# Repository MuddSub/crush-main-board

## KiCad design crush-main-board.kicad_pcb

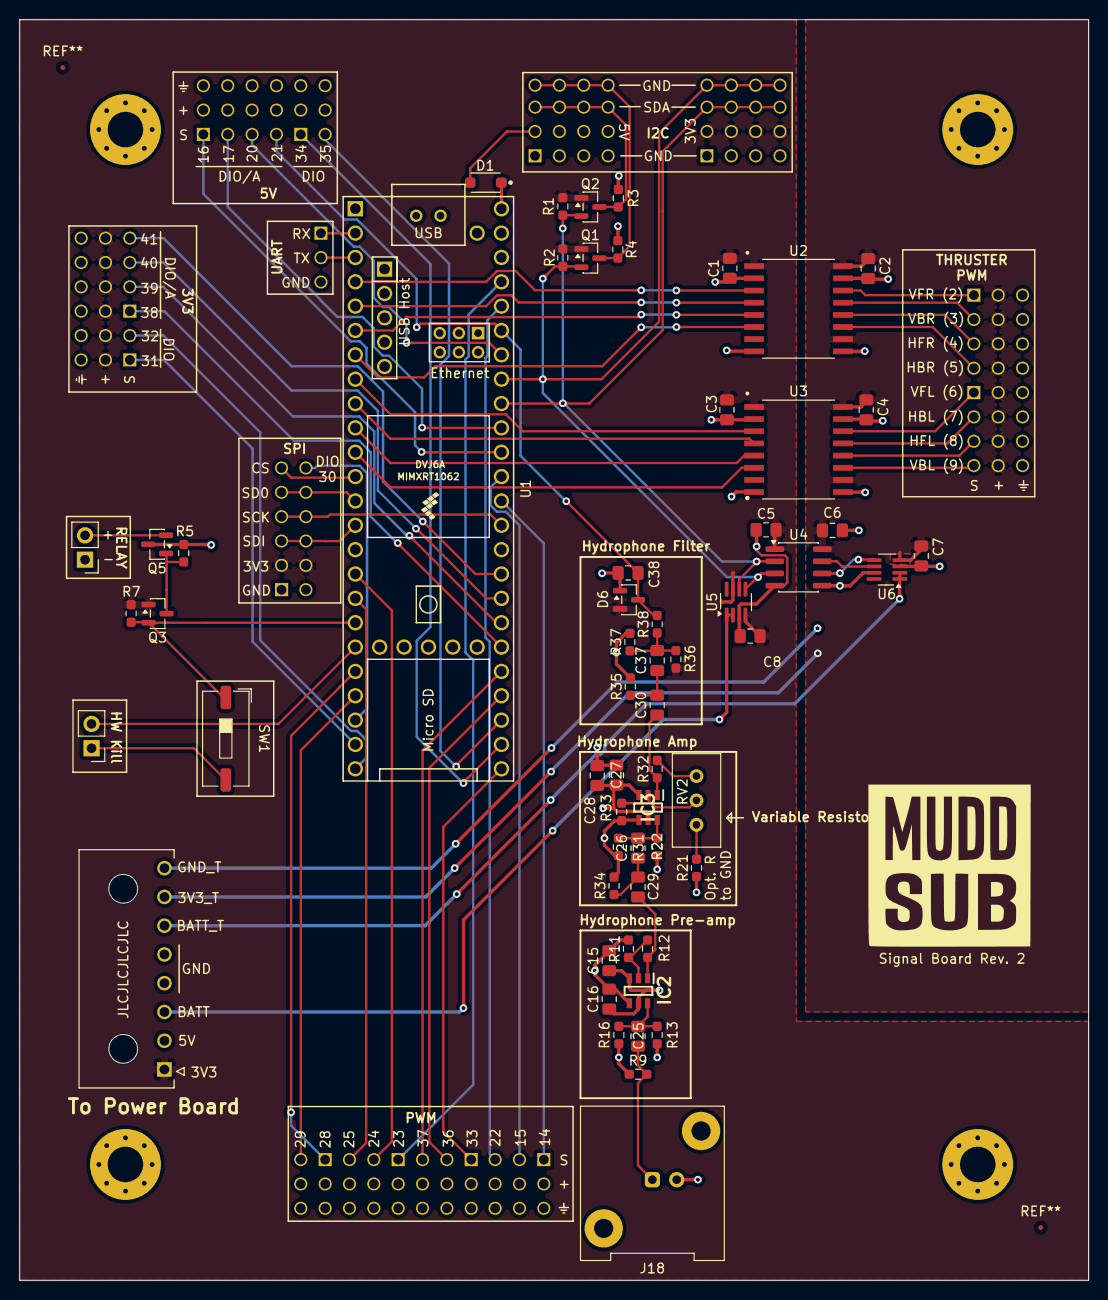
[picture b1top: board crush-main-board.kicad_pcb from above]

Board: 4 copper layers, 111.5 x 131.5 mm, 77 parts (0 on the bottom side), 77 nets.

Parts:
C1, C2, C3, C4, C5, C6, C7, C8: 0u1; C_0805_2012Metric_Pad1.18x1.45mm_HandSolder
C15, C27: 100n; C_0805_2012Metric_Pad1.18x1.45mm_HandSolder
C16, C28, C29, C30: 10n; C_0805_2012Metric_Pad1.18x1.45mm_HandSolder
C25, C26, C37: 1m; C_0805_2012Metric_Pad1.18x1.45mm_HandSolder
C38: 2.2n; C_0805_2012Metric_Pad1.18x1.45mm_HandSolder
D1: SM5817PL-TP; SODFL3718X108N
D6: BAT54S; SOT-23
H1, H2, H3, H4: MountingHole_Pad; MountingHole_3.7mm_Pad_Via
IC2, IC3: LT6200CS6#TRMPBF; SOT95P280X100-6N
J1, J2: 4x4_Header
J3: 6x2_Header
J4: 3x1_Header
J5, J6, J12: 3x2 Header; 3x2_Header
J7, J8: 3x4 Header; 3x4_Header
J9, J10, J11: 3x3 Header; 3x3_Header
J13, J14: 3x4_Header
J15: 2157601008; MOLEX_2157601008
J16, J17: Conn_01x02; PinHeader_1x02_P2.54mm_Vertical
J18: Conn_Coaxial; BNC_Amphenol_031-5539_Vertical
Q1, Q2, Q3: BSN20; SOT-23
Q5: DMG2301L; SOT-23
R1, R2, R3, R4, R5, R7: 2k4; R_0603_1608Metric_Pad0.98x0.95mm_HandSolder
R9: r=50; R_0603_1608Metric_Pad0.98x0.95mm_HandSolder
R11, R16, R31, R33: 1k; R_0603_1608Metric_Pad0.98x0.95mm_HandSolder
R12, R13, R32, R34, R35: 100k; R_0603_1608Metric_Pad0.98x0.95mm_HandSolder
R21: r=100k; R_0603_1608Metric_Pad0.98x0.95mm_HandSolder
R22: 1Meg; R_0603_1608Metric_Pad0.98x0.95mm_HandSolder
R36, R37: 10k; R_0603_1608Metric_Pad0.98x0.95mm_HandSolder
R38: r=1k; R_0603_1608Metric_Pad0.98x0.95mm_HandSolder
RV2: R_Potentiometer_Trim; Potentiometer_Bourns_3296W_Vertical
SW1: SW_SPST; SW_DIP_SPSTx01_Slide_9.78x4.72mm_W8.61mm_P2.54mm
U1: Teensy4.1; Teensy41
U2, U3: ISO7740DW; SOIC127P1030X265-16N
U4: ISO1640BDR; SOIC-8_3.9x4.9mm_P1.27mm
U5, U6: INA232B; SOT-23-8_Handsoldering

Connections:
+3V3: C1.2, C3.2, C5.2, C8.2, D6.2 (K), J1.02, J1.06, J1.10, J1.14, J3.02, J3.08, J5.02, J5.05, J7.02, J7.05, J7.08, J7.11, J15.1, Q1.1 (G), Q2.1 (G), Q3.1 (G), R1.1, R2.1, R7.1, R36.1, U2.1 (VCC1), U3.1 (VCC1), U4.1 (VCC1), U5.4 (VS), U5.7 (A0)
+3V3_T: C2.2, C4.2, C6.2, C7.2, J13.02, J13.05, J13.08, J13.11, J14.02, J14.05, J14.08, J14.11, J15.7, U2.10 (EN2), U2.16 (VCC2), U3.10 (EN2), U3.16 (VCC2), U4.8 (VCC2), U6.4 (VS)
+5V: C15.1, C16.1, C27.1, C28.1, D1.2 (A), IC2.3 (+IN), IC2.5 (~SHDN), IC3.3 (+IN), IC3.5 (~SHDN), J2.02, J2.06, J2.10, J2.14, J6.02, J6.05, J8.02, J8.05, J8.08, J8.11, J9.02, J9.05, J9.08, J10.02, J10.05, J10.08, J11.02, J11.05, J11.08, J12.02, J12.05, J15.2, Q5.3 (D), R3.1, R4.1, R5.1, R13.1, R22.1
/+RELAY: J17.2, Q5.2 (S)
/SCL_T: U4.6 (SCL2), U6.5 (SCL)
/SDA_T: U4.7 (SDA2), U6.6 (SDA)
A/DIO16: J8.01, U1.38 (16_A2_RX4_SCL1)
A/DIO17: J8.04, U1.39 (17_A3_TX4_SDA1)
A/DIO20: J8.07, U1.42 (20_A6_TX5_LRCLK1)
A/DIO21: C38.1, D6.3 (COM), J8.10, R38.2, U1.43 (21_A7_RX5_BCLK1)
A/DIO26: Q3.2 (S), R7.2, SW1.1 (A), U1.18 (26_A12_MOSI1)
A/DIO38: J7.01, U1.30 (38_CS1_IN1)
A/DIO39: J7.04, U1.31 (39_MISO1_OUT1A)
A/DIO40: J7.07, U1.32 (40_A16)
A/DIO41: J7.10, U1.33 (41_A17)
BATT: J15.3, U5.1 (Vin+), U5.2 (Vin-)
BATT_T: J15.6, U6.1 (Vin+), U6.2 (Vin-)
BNC_OUT: C25.1, J18.1 (In), R9.2
DIO30: J3.12, U1.22 (30_CRX3)
DIO31: J5.01, U1.23 (31_CTX3)
DIO32: J5.04, U1.24 (32_OUT1B)
DIO34: J6.01, U1.26 (34_RX8)
DIO35: J6.04, U1.27 (35_TX8)
GND: C1.1, C3.1, C5.1, C8.1, C15.2, C16.2, C27.2, C28.2, C38.2, D6.1 (A), H1.1 (1_1), H2.1 (1_1), H3.1 (1_1), H4.1 (1_1), IC2.4 (-IN), IC3.4 (-IN), J1.01, J1.05, J1.09, J1.13, J2.01, J2.05, J2.09, J2.13, J3.01, J3.07, J4.03, J5.03, J5.06, J6.03, J6.06, J7.03, J7.06, J7.09, J7.12, J8.03, J8.06, J8.09, J8.12, J9.03, J9.06, J9.09, J10.03, J10.06, J10.09, J11.03, J11.06, J11.09, J12.03, J12.06, J15.5, J17.1, J18.2 (Ext), R9.1, R11.2, R16.2, R21.1, R31.2, R33.2, R34.2, R35.2, R37.2, U1.1 (GND), U1.34 (GND), U1.47 (GND), U1.58 (GND), U1.59 (GND), U2.2 (GND1), U2.8 (GND1), U3.2 (GND1), U3.8 (GND1), U4.4 (GND1), U5.3 (GND)
GND_T: C2.1, C4.1, C6.1, C7.1, J13.03, J13.06, J13.09, J13.12, J14.03, J14.06, J14.09, J14.12, J15.8, U2.9 (GND2), U2.15 (GND2), U3.9 (GND2), U3.15 (GND2), U4.5 (GND2), U6.3 (GND), U6.7 (A0)
HW_KILL_1: J16.2, U1.19 (27_A13_SCK1)
HW_KILL_2: J16.1, SW1.2 (B)
unnamed: C26.1, C29.2, R34.1
unnamed: C30.2, C37.1, R35.1
unnamed: C37.2, R36.2, R37.1, R38.1
unnamed: D1.1 (K), U1.48 (VIN)
unnamed: C25.2, IC2.6 (V+), R13.2, R16.1
unnamed: IC2.2 (V-), R11.1, R12.2
unnamed: C26.2, IC3.6 (V+), R22.2, R31.1
unnamed: IC3.2 (V-), R33.1, RV2.2
unnamed: Q3.3 (D), Q5.1 (G), R5.2
unnamed: R21.2, RV2.3
unnamed: R32.2, RV2.1
PWM2: U1.4 (2_OUT2), U2.3 (INA)
PWM2_T: J13.01, U2.14 (OUTA)
PWM3: U1.5 (3_LRCLK2), U2.4 (INB)
PWM3_T: J13.04, U2.13 (OUTB)
PWM4: U1.6 (4_BCLK2), U2.5 (INC)
PWM4_T: J13.07, U2.12 (OUTC)
PWM5: U1.7 (5_IN2), U2.6 (IND)
PWM5_T: J13.10, U2.11 (OUTD)
PWM6: U1.8 (6_OUT1D), U3.3 (INA)
PWM6_T: J14.01, U3.14 (OUTA)
PWM7: U1.9 (7_RX2_OUT1A), U3.4 (INB)
PWM7_T: J14.04, U3.13 (OUTB)
PWM8: U1.10 (8_TX2_IN1), U3.5 (INC)
PWM8_T: J14.07, U3.12 (OUTC)
PWM9: U1.11 (9_OUT1C), U3.6 (IND)
PWM9_T: J14.10, U3.11 (OUTD)
PWM14: J9.01, U1.36 (14_A0_TX3_SPDIF_OUT)
PWM15: J9.04, U1.37 (15_A1_RX3_SPDIF_IN)
PWM22: J9.07, U1.44 (22_A8_CTX1)
PWM23: J10.01, U1.45 (23_A9_CRX1_MCLK1)
PWM24: J10.04, U1.16 (24_A10_TX6_SCL2)
PWM25: J10.07, U1.17 (25_A11_RX6_SDA2)
PWM28: J12.01, U1.20 (28_RX7)
PWM29: J12.04, U1.21 (29_TX7)
PWM33: J11.01, U1.25 (33_MCLK2)
PWM36: J11.04, U1.28 (36_CS)
PWM37: J11.07, U1.29 (37_CS)
SCL_3V3: J1.04, J1.08, J1.12, J1.16, Q1.2 (S), R2.2, U1.41 (19_A5_SCL), U4.3 (SCL1), U5.5 (SCL)
SCL_5V: J2.04, J2.08, J2.12, J2.16, Q1.3 (D), R4.2
SDA_3V3: J1.03, J1.07, J1.11, J1.15, Q2.2 (S), R1.2, U1.40 (18_A4_SDA), U4.2 (SDA1), U5.6 (SDA)
SDA_5V: J2.03, J2.07, J2.11, J2.15, Q2.3 (D), R3.2
SPI_CS: J3.06, U1.12 (10_CS_MQSR)
SPI_SCK: J3.04, J3.10, U1.35 (13_SCK_LED)
SPI_SDI: J3.03, J3.09, U1.14 (12_MISO_MQSL)
SPI_SDO: J3.05, J3.11, U1.13 (11_MOSI_CTX1)
UART_RX: J4.01, U1.2 (0_RX1_CRX2_CS1)
UART_TX: J4.02, U1.3 (1_TX1_CTX2_MISO1)
VOUT_AMP: C30.1, IC3.1 (OUT), R32.1
VOUT_PREAMP: C29.1, IC2.1 (OUT), R12.1

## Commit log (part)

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2023-02-26 First Commit, WIP
2023-02-27 2/26 Work as a team
2023-02-27 baby change to test committing
2023-02-27 deleted unnecessary files
2023-03-12 Added Digital Isolators
2023-03-26 Add labels for teensy ports
2023-03-26 Update custom library and add PWM headers
2023-03-27 Library Update
    Add the footprint library named "Crush_Mainboard_Footprints.pretty" in the library folder
2023-03-27 Header Arrangement
    Add headers for the remaining pins and attach the custom footprints
2023-03-31 Cleaned up the repo and added Teensy 4.1 to the Crush project library
2023-04-01 Deleted some unnecessary files that were renamed
2023-04-02 Update library with default footprints
2023-04-03 Add SPI, UART, ESC Headers; Fixed library stuff
2023-04-03 Fixed .gitignore and removed backup folders from repo
2023-04-03 Cleaned up the schematic layout & separated the footprints into corresponding groups
2023-04-03 Clean up some minor details in the symbol and footprint library
2023-04-09 Fixed SPI header and updated footprint accordingly
2023-04-10 Removed USB connector (deemed unnecessary) as well as added infrastructure for a battery monitoring circuit
2023-04-10 Added thruster battery monitoring circuit
    There is no footprint assigned for an I2C isolator and resistors yet
2023-04-10 fixed some minor error
2023-04-10 added electrical side battery monitor in case we don't use Teensy's ADC
2023-04-17 Added diode and header for remaining pins, fixed signal battery monitor
2023-04-17 Changed resistor and capacitor footprints to 0603
2023-04-23 Added library for MOLEX inter-board connector
2023-04-23 Added connection to the power board; and the remaining footprints
2023-04-24 Fixed an error of the "3V3_T" and "GND_T" and added some conditions for the PCB design
    The power nets for the thruster side require their own custom symbols unless they will refer to the same ones that are linked to the normal power nets
2023-04-25 Fixed some minor errors and arranged the components into two ground sides
2023-04-26 arranged all components to be ready for routing
2023-04-27 re-aligned the elements based on their grounds
2023-09-30 update i2c level shifter
    * Change resistors from 4.7k to 2.4k to improve signal quality
    * Connect SCL MOSFET gate to 3.3V rather than 5V
2023-11-04 Add battery monitoring circuit using INA233
2023-11-04 minor visual change
2023-11-04 Add shunt capacitor for INA233
2023-11-04 Sketch out a possible circuit for the killswitch
2023-11-11 Switch to INA232
2023-11-18 Fix killswitch circuit
2023-11-18 Fix overlapping wires
2023-11-18 Add levelshifter textbox label
2023-12-02 Changed driving of relay to account for relay loading
2024-02-17 Updated reference for current monitoring chip
2024-02-17 Added JLCPCB Design Rule Check
2024-02-18 Wire up the relay killswitch with JSTs
    In the schematic
2024-02-25 Start laying out main board
2024-03-23 Add monitor for signal battery
2024-03-23 Add changes to pcb
2024-04-06 fixed janky wire in killswitch subcircuit
2024-04-06 Fixed import issues from sch to pcb
2024-04-06 basic routing
2024-04-08 place mounting holes
2024-04-08 force solid mounting pad connections
2024-04-13 precise component layout
2024-04-13 placement updates
2024-04-13 fix thruster headers
2024-04-13 schematic net fixes
2024-04-13 routing
2024-04-13 more schematic fixes
2024-04-13 fix unconnected components
2024-04-13 move trace
2024-04-20 Updated main board for better bypass caps & routing review
2024-05-04 cleanup traces
2024-05-04 silkscreen
2024-05-04 add JLC order number location
2024-09-21 add CODEOWNERS file
2024-09-28 add additional labeling to io ports
2024-09-28 use + instead of V for vcc
2024-09-28 update i2c pin order
2024-11-18 use 0805 footprints for decoupling capacitors
2025-02-09 move c7 cap
2025-10-26 convert from 2 -> 4 layer board, reduce vias and traces, currently no errors when running DRC
2025-11-02 Add Rocker E-Switch footprint to Crush library.
2025-11-02 Route 3V3, 3V3, and 5V sources from power board through AND gates, with second input from 3V3, routed through Rocker E-Switch
2025-11-07 Remove 90-degree track
2025-11-07 Remove copper fill islands
2025-11-09 Add local corner fiducials, extend board to allow for 5 mm of fiducial clearance (which likely should be decreased), and add 5 initial test points
2025-11-16 Move testpoints to back of board, add testpoint at manual kill switch 5V output
2025-11-16 Update main board with autosave updates
2025-11-22 Add signal test points
2025-11-23 Add teardrops to PTH, SMD, and vias
2026-02-15 Removed AND gate kill switch, added HW_KILL_3 and HW_KILL_4 in series in front of kill switch relay, changed net ground plane from BATT to GND (fix), removed kill switch footprint
2026-02-21 Swapped HW and manual kill switches, set manual kill switch reference value to SW1
2026-03-08 added bnc connector
2026-04-06 Add simulation circuit for Hydrophone Preamp (Stage 1)
2026-04-06 Add schematic circuit for Hydrophone Preamp (Stage 1)
2026-04-09 Set trimpot sim model to KiCad built-in resistor potentiometer model, added amp subsheet to main sheet
2026-04-10 Add hydrophone filter sim circuit and subsheet (Stage 3)
2026-04-11 Added footprints and ROUGH PCB placements/routing
2026-04-11 Add -5V pin (pin 4) to power board connection
2026-04-11 Add BNC connection to VIN of hydrophone pre-amp subcircuit
2026-04-29 Change op amps to single-supply LT6200
2026-05-02 Arranged all components off-board; considering swapping manual kill into empty space on bottom right corner to make room for hydrophone near A/DIO pins
2026-05-03 Add hydrophone preamp/amp/filter stages to PCB
